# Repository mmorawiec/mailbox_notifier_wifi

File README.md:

# mailbox_notifier_wifi
 ESP8266 based WiFi notification

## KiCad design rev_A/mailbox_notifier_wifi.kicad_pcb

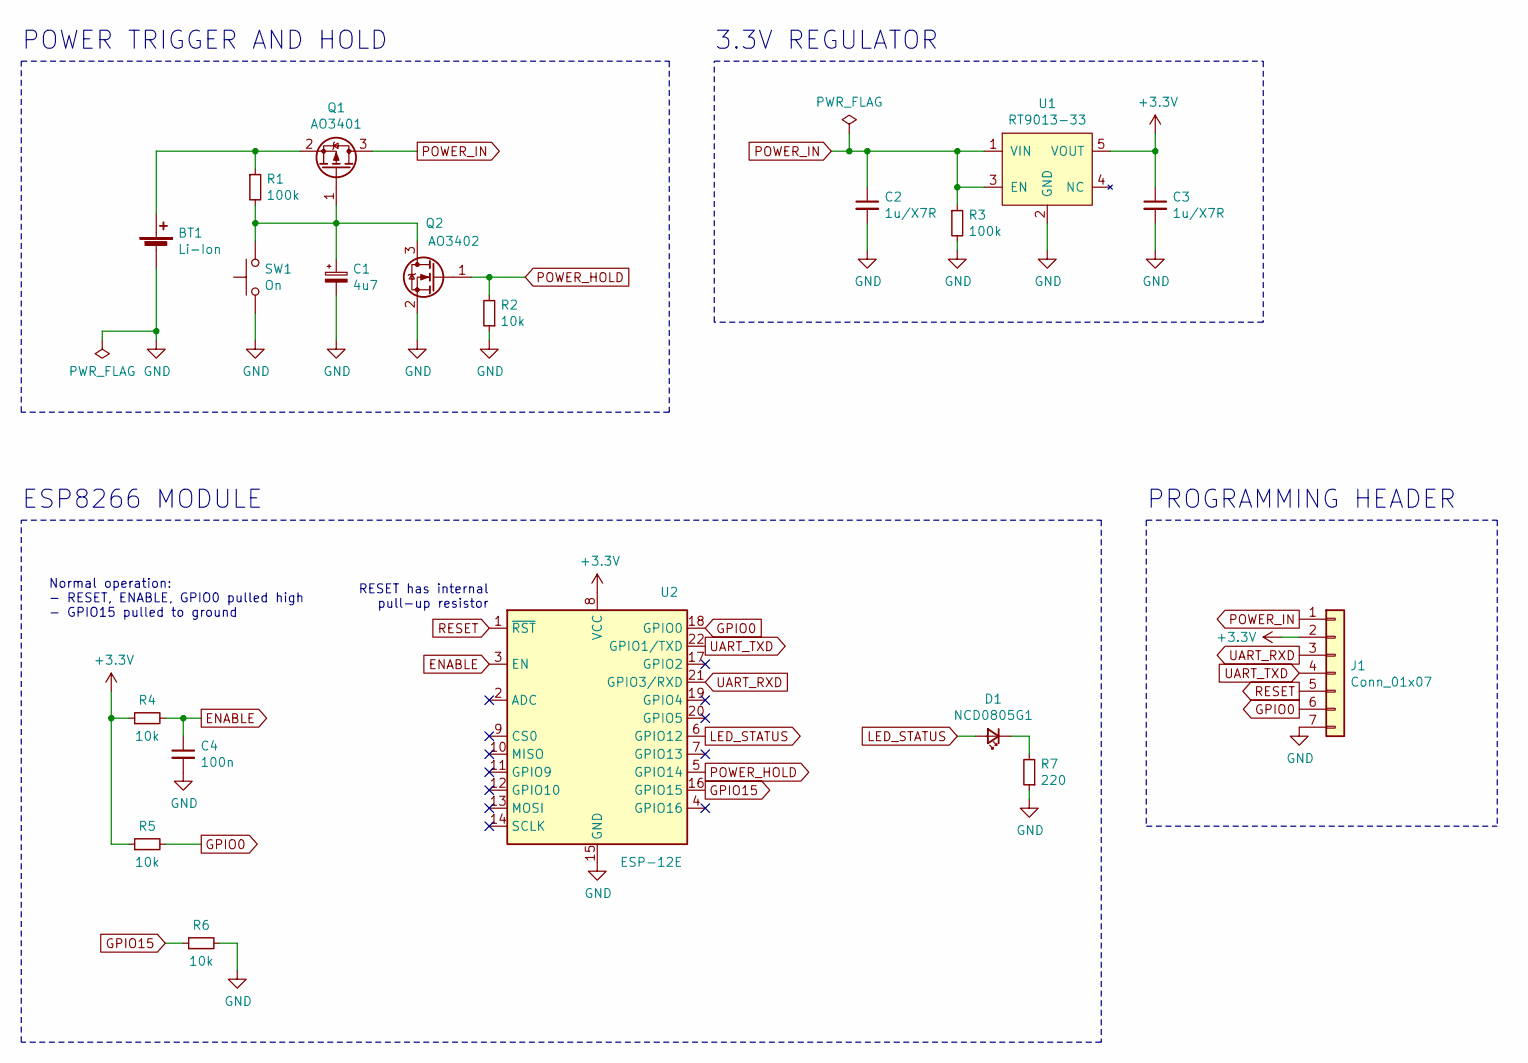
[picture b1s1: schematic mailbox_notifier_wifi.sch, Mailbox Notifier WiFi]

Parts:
BT1: Li-Ion; PinHeader_1x02_P2.54mm_Vertical
C1: 4u7; CP_Elec_4x5.4; LCSC C128465
C2, C3: 1u/X7R; C_0805_2012Metric; LCSC C28323
C4: 100n; C_0805_2012Metric; LCSC C49678
D1: NCD0805G1; LED_0805_2012Metric; LCSC C84260
J1: Conn_01x07; PinHeader_1x07_P2.54mm_Horizontal
Q1: AO3401; SOT-23; LCSC C15127
Q2: AO3402; SOT-23; LCSC C14385
R1, R3: 100k; R_0805_2012Metric; LCSC C17407
R2, R4, R5, R6: 10k; R_0805_2012Metric; LCSC C17414
R7: 220; R_0805_2012Metric; LCSC C17557
SW1: On; PinHeader_1x02_P2.54mm_Horizontal
U1: RT9013-33; SOT-23-5; LCSC C47773
U2: ESP-12E

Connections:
+3V3: C3.1, J1.2, R4.1, R5.1, U1.5 (VOUT), U2.8 (VCC)
ENABLE: C4.1, R4.2, U2.3 (EN)
GND: BT1.2 (-), C1.2, C2.2, C3.2, C4.2, J1.7, Q2.2 (S), R2.1, R3.2, R6.2, R7.1, SW1.1, U1.2 (GND), U2.15 (GND)
GPIO0: J1.6, R5.2, U2.18 (GPIO0)
GPIO15: R6.1, U2.16 (GPIO15)
LED_STATUS: D1.2 (A), U2.6 (GPIO12)
unnamed: BT1.1 (+), Q1.2 (S), R1.1
unnamed: C1.1, Q1.1 (G), Q2.3 (D), R1.2, SW1.2
unnamed: D1.1 (K), R7.2
POWER_HOLD: Q2.1 (G), R2.2, U2.5 (GPIO14)
POWER_IN: C2.1, J1.1, Q1.3 (D), R3.1, U1.1 (VIN), U1.3 (EN)
RESET: J1.5, U2.1 (~RST)
UART_RXD: J1.3, U2.21 (GPIO3/RXD)
UART_TXD: J1.4, U2.22 (GPIO1/TXD)

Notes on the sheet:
RESET has internal pull-up resistor
Normal operation: - RESET, ENABLE, GPIO0 pulled high - GPIO15 pulled to ground
ESP8266 MODULE
POWER TRIGGER AND HOLD
3.3V REGULATOR
PROGRAMMING HEADER

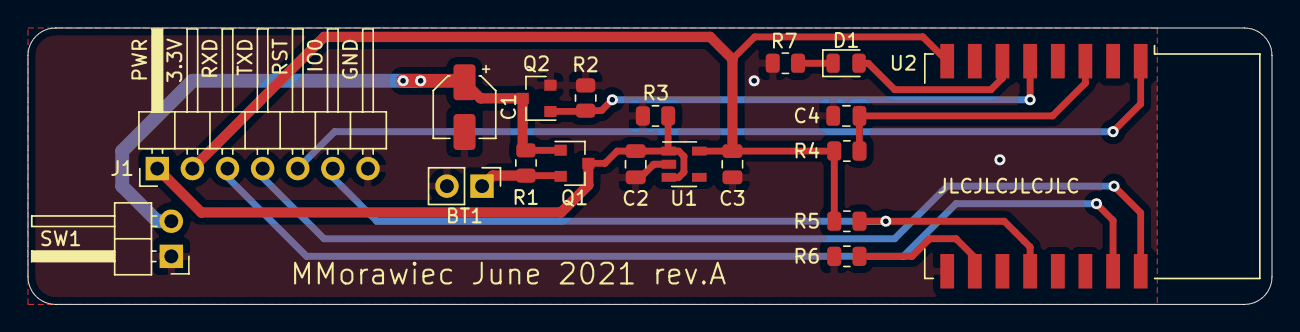
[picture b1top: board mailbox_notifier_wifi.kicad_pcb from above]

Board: 2 copper layers, 90.0 x 20.0 mm, 19 parts (0 on the bottom side), 14 nets.

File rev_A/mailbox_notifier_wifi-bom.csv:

Comment,Designator,Footprint,LCSC
"4u7","C1","Capacitor_SMD:CP_Elec_4x5.4","C128465"
"1u/X7R","C2,C3","Capacitor_SMD:C_0805_2012Metric","C28323"
"100n","C4","Capacitor_SMD:C_0805_2012Metric","C49678"
"NCD0805G1","D1","LED_SMD:LED_0805_2012Metric","C84260"
"AO3401","Q1","Package_TO_SOT_SMD:SOT-23","C15127"
"AO3402","Q2","Package_TO_SOT_SMD:SOT-23","C14385"
"100k","R1,R3","Resistor_SMD:R_0805_2012Metric","C17407"
"10k","R2,R4,R5,R6","Resistor_SMD:R_0805_2012Metric","C17414"
"220","R7","Resistor_SMD:R_0805_2012Metric","C17557"
"RT9013-33","U1","Package_TO_SOT_SMD:SOT-23-5","C47773"

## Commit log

2021-07-17 Allow csv files
2021-07-17 Add bom and pos files
